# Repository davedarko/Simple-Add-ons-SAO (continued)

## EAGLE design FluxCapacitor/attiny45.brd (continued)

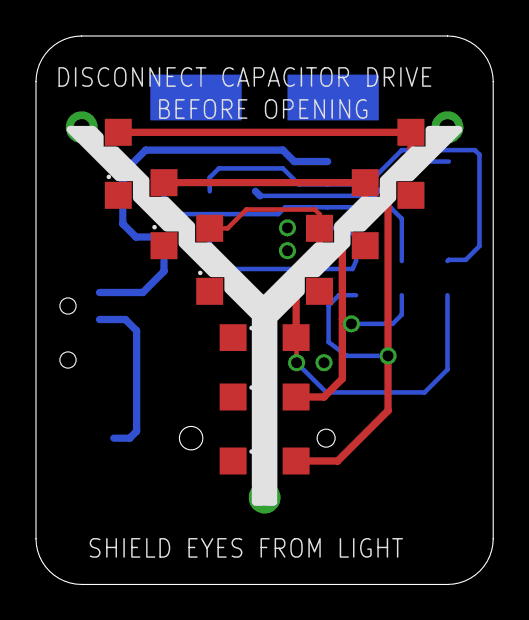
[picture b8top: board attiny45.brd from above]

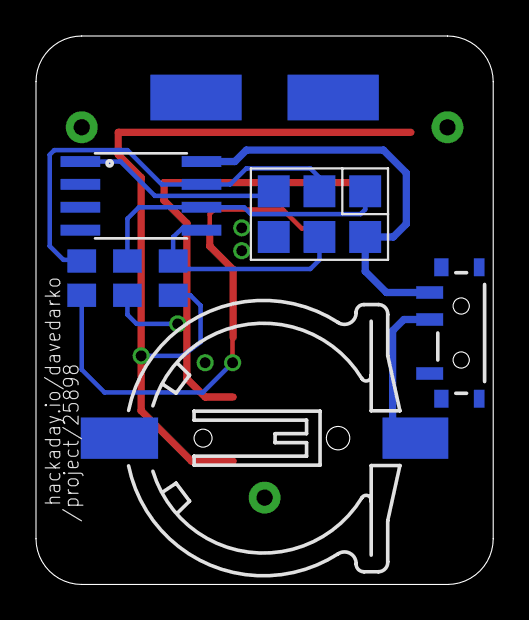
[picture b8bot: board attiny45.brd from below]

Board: 2 copper layers, 25.4 x 30.5 mm, 16 parts (7 on the bottom side), 10 nets.

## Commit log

2022-10-18 Update .gitignore
    added eagle bits
2022-10-18 remove mac stuff
2022-10-18 removed backups
2022-10-18 covid19 test sao
2022-10-18 library stick for SAOs
2022-10-18 vendettaSAO
2022-10-18 Mr Robot Badge with Code
2022-10-19 added phengicorn SAO badge
    found it on the penghicorn repo
2022-10-21 wrong file name
2022-11-14 moved labels, gerber version 3 for HiP.berlin
2023-11-15 added more SAO
2024-09-05 added more SAOs and converted to Kicad8
2024-09-05 kitt SAO
2024-10-05 added 2 more and updated solo
2024-10-11 updated production HelloMyNameIs
2024-11-03 slides
2026-05-19 Added more designs and updates
2026-05-21 added LECCO
